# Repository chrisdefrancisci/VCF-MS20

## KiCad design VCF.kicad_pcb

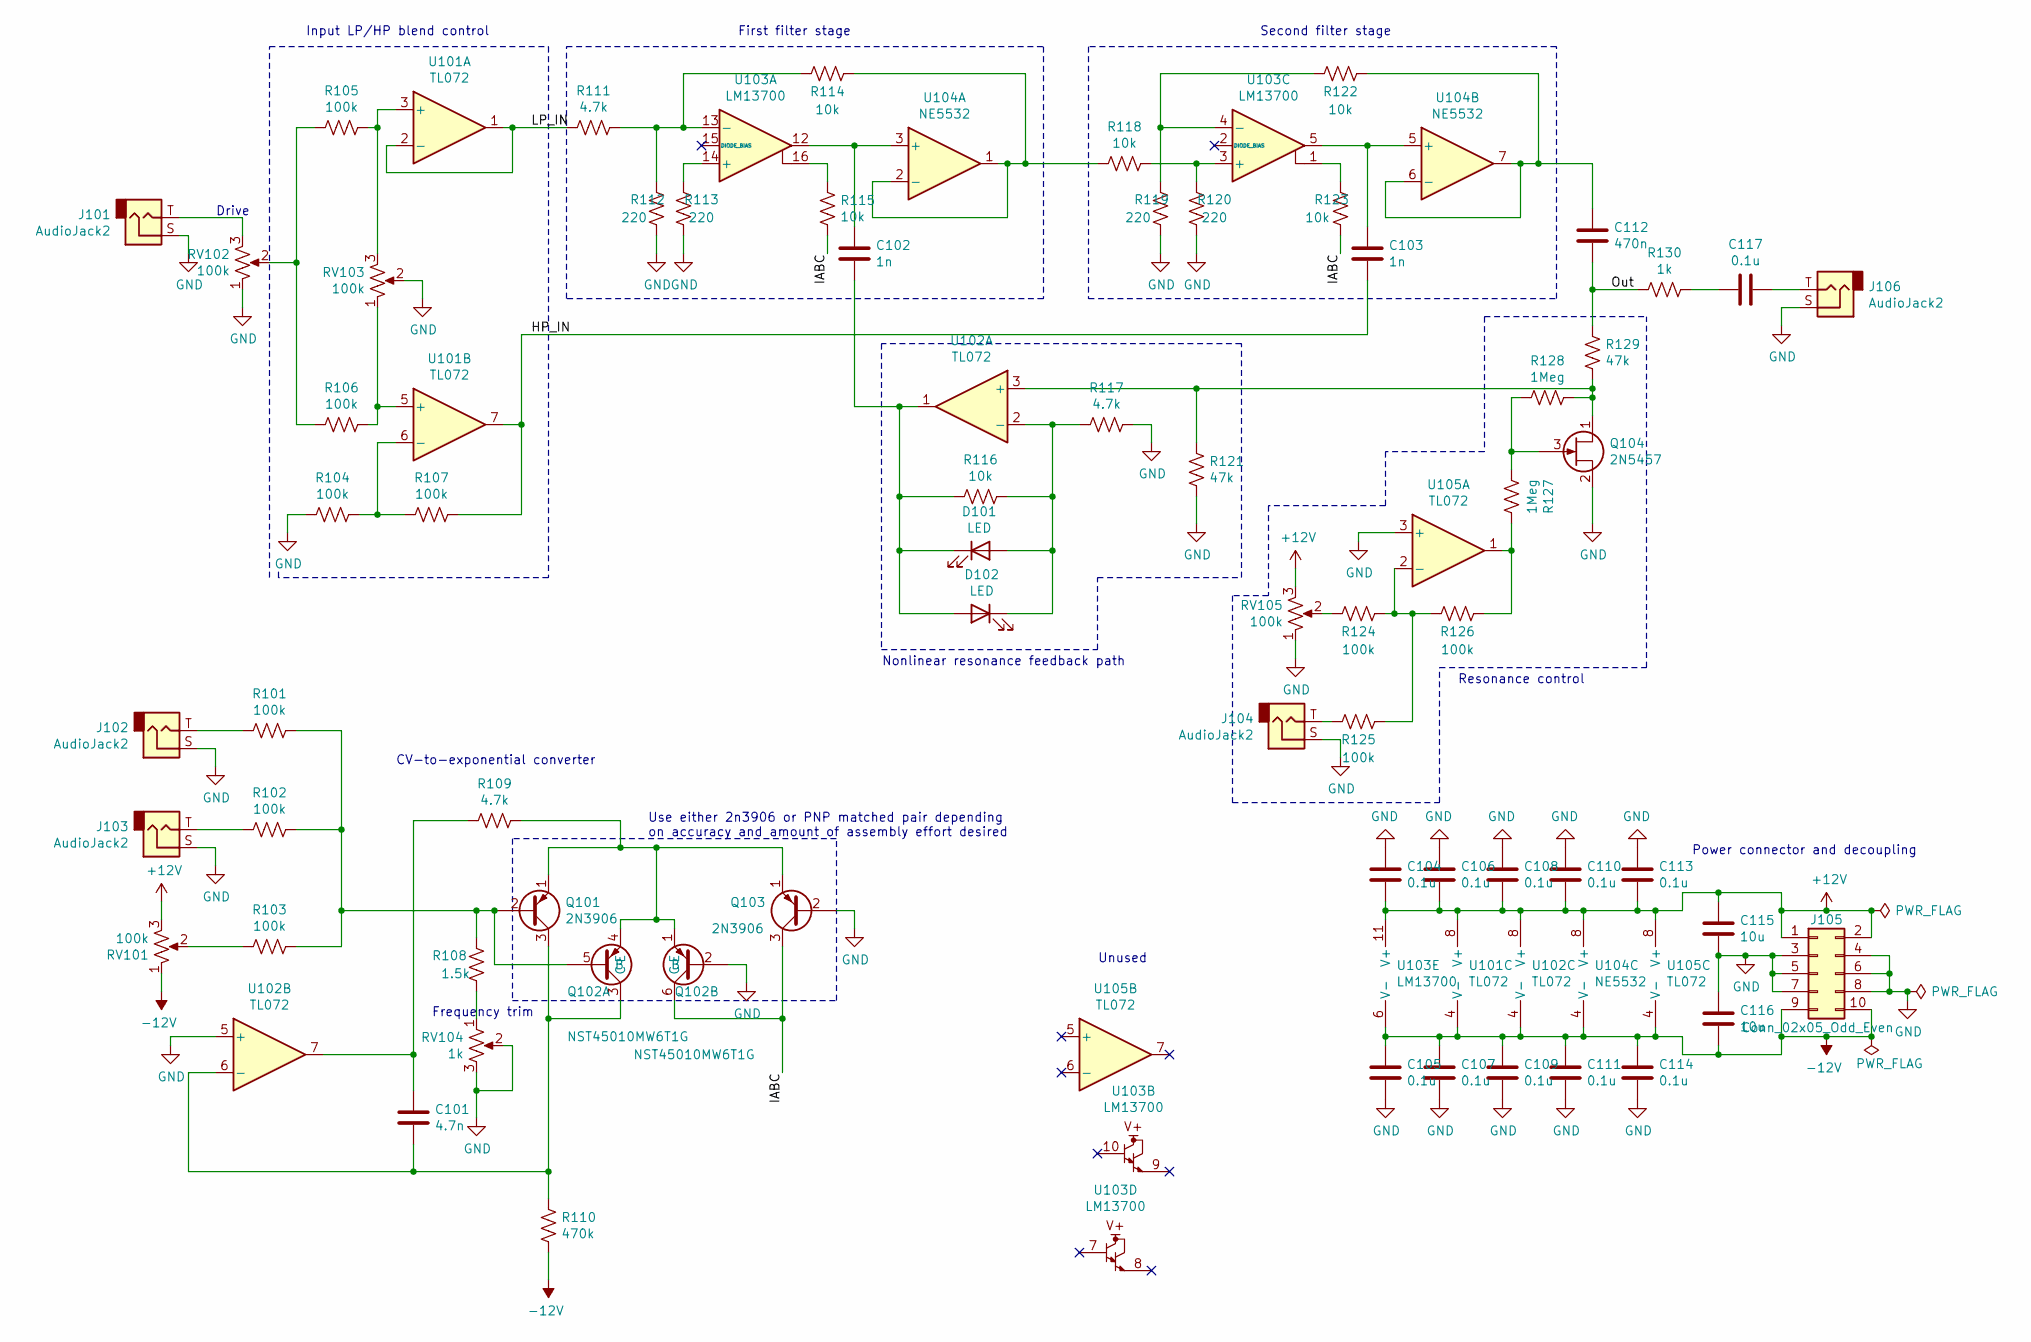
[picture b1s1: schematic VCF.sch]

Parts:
C101: 4.7n; C_0402_1005Metric; LCSC C1538
C102, C103: 1n; C_0402_1005Metric; LCSC C1523
C104, C105, C106, C107, C108, C109, C110, C111, C113, C114, C117: 0.1u; C_0402_1005Metric; LCSC C1525
C112: 470n; C_0402_1005Metric; LCSC C47339
C115, C116: 10u; C_0402_1005Metric; LCSC C15525
D101, D102: LED; LED_D5.0mm
J101, J102, J103, J104, J106: AudioJack2; A-2563
J105: Conn_02x05_Odd_Even; PinHeader_2x05_P2.54mm_Vertical
Q101, Q103: 2N3906; TO-92_Inline
Q102: NST45010MW6T1G; SOT-363_SC-70-6_Handsoldering
Q104: 2N5457; TO-92_Inline
R101, R102, R103, R104, R105, R106, R107, R124, R125, R126: 100k; R_0402_1005Metric; LCSC C25741
R108: 1.5k; R_0402_1005Metric; LCSC C25867
R109, R111, R117: 4.7k; R_0402_1005Metric; LCSC C25900
R110: 470k; R_0402_1005Metric; LCSC C25792
R112, R113, R119, R120: 220; R_0402_1005Metric; LCSC C25091
R114, R115, R116, R118, R122, R123: 10k; R_0402_1005Metric; LCSC C25744
R121, R129: 47k; R_0402_1005Metric; LCSC C25792
R127, R128: 1Meg; R_0402_1005Metric; LCSC C26083
R130: 1k; R_0402_1005Metric; LCSC C11702
RV101, RV102, RV103, RV105: 100k; A-5513
RV104: 1k; Potentiometer_Bourns_3296X_Horizontal
U101, U102, U105: TL072; SOIC-8_3.9x4.9mm_P1.27mm; LCSC C6961
U103: LM13700; DIP-16_W7.62mm
U104: NE5532; SOIC-8_3.9x4.9mm_P1.27mm; LCSC C7426

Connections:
+12V: C104.2, C106.2, C108.2, C110.2, C113.2, C115.1, J105.1, J105.2, RV101.3, RV105.3, U101.8 (V+), U102.8 (V+), U103.11 (V+), U104.8 (V+), U105.8 (V+)
-12V: C105.1, C107.1, C109.1, C111.1, C114.1, C116.2, J105.9, J105.10, R110.2, RV101.1, U101.4 (V-), U102.4 (V-), U103.6 (V-), U104.4 (V-), U105.4 (V-)
/HP_IN: C103.2, R107.1, U101.7
/IABC: Q102.6 (C), Q103.3 (C), R115.2, R123.2
/LP_IN: R111.2, U101.1, U101.2 (-)
/Out: C112.1, R129.2, R130.2
GND: C104.1, C105.2, C106.1, C107.2, C108.1, C109.2, C110.1, C111.2, C113.1, C114.2, C115.2, C116.1, J101.S, J102.S, J103.S, J104.S, J105.3, J105.4, J105.5, J105.6, J105.7, J105.8, J106.S, Q102.2 (B), Q103.2 (B), Q104.2 (S), R104.2, R112.2, R113.2, R117.2, R119.2, R120.2, R121.1, RV102.1, RV103.2, RV104.2, RV104.3, RV105.1, U102.5 (+), U105.3 (+)
unnamed: C101.1, R109.2, U102.7
unnamed: C101.2, Q101.3 (C), Q102.3 (C), R110.1, U102.6 (-)
unnamed: C102.1, U103.12, U104.3 (+)
unnamed: C102.2, D101.1 (K), D102.2 (A), R116.2, U102.1
unnamed: C103.1, U103.5, U104.5 (+)
unnamed: C112.2, R122.1, U104.6 (-), U104.7
unnamed: C117.1, J106.T
unnamed: C117.2, R130.1
unnamed: D101.2 (A), D102.1 (K), R116.1, R117.1, U102.2 (-)
unnamed: J101.T, RV102.3
unnamed: J102.T, R101.2
unnamed: J103.T, R102.2
unnamed: J104.T, R125.1
unnamed: Q101.1 (E), Q102.1 (E), Q102.4 (E), Q103.1 (E), R109.1
unnamed: Q101.2 (B), Q102.5 (B), R101.1, R102.1, R103.1, R108.1
unnamed: Q104.1 (D), R121.2, R128.1, R129.1, U102.3 (+)
unnamed: Q104.3 (G), R127.2, R128.2
unnamed: R103.2, RV101.2
unnamed: R104.1, R107.2, U101.6 (-)
unnamed: R105.1, RV103.3, U101.3 (+)
unnamed: R105.2, R106.2, RV102.2
unnamed: R106.1, RV103.1, U101.5 (+)
unnamed: R108.2, RV104.1
unnamed: R111.1, R112.1, R114.2, U103.13 (-)
unnamed: R113.1, U103.14 (+)
unnamed: R114.1, R118.2, U104.1, U104.2 (-)
unnamed: R115.1, U103.16
unnamed: R118.1, R120.1, U103.3 (+)
unnamed: R119.1, R122.2, U103.4 (-)
unnamed: R123.1, U103.1
unnamed: R124.1, RV105.2
unnamed: R124.2, R125.2, R126.1, U105.2 (-)
unnamed: R126.2, R127.1, U105.1

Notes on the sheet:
Input LP/HP blend control
Drive
First filter stage
Second filter stage
Resonance control
Nonlinear resonance feedback path
CV-to-exponential converter
Unused
Power connector and decoupling
Frequency trim
Use either 2n3906 or PNP matched pair depending on accuracy and amount of assembly effort desired

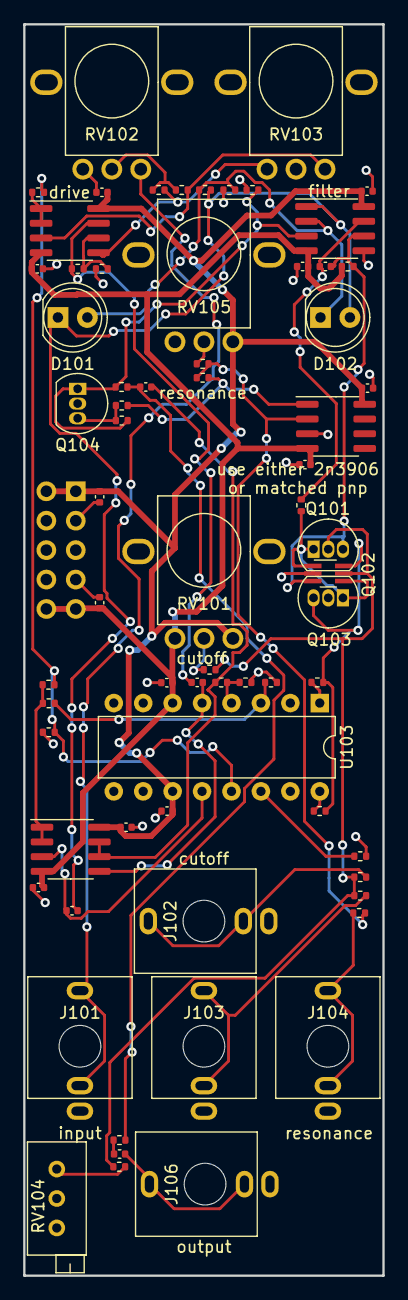
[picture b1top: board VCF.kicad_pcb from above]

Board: 2 copper layers, 31.0 x 108.0 mm, 69 parts (1 on the bottom side), 40 nets.

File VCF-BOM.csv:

Comment,Designator,Footprint,LCSC
"4.7n","C101","Capacitor_SMD:C_0402_1005Metric","C1538"
"1n","C102,C103","Capacitor_SMD:C_0402_1005Metric","C1523"
"470n","C112","Capacitor_SMD:C_0402_1005Metric","C47339"
"10u","C115,C116","Capacitor_SMD:C_0402_1005Metric","C15525"
"0.1u","C104,C105,C106,C107,C108,C109,C110,C111,C113,C114,C117","Capacitor_SMD:C_0402_1005Metric","C1525"
"LED","D101,D102","LED_THT:LED_D5.0mm",""
"AudioJack2","J101,J102,J103,J104,J106","A-2563:A-2563",""
"Conn_02x05_Odd_Even","J105","Connector_PinHeader_2.54mm:PinHeader_2x05_P2.54mm_Vertical",""
"NST45010MW6T1G","Q102","Package_TO_SOT_SMD:SOT-363_SC-70-6_Handsoldering",""
"2N3906","Q101,Q103","Package_TO_SOT_THT:TO-92_Inline",""
"2N5457","Q104","Package_TO_SOT_THT:TO-92_Inline",""
"100k","R101,R102,R103,R104,R105,R106,R107,R124,R125,R126","Resistor_SMD:R_0402_1005Metric","C25741"
"1.5k","R108","Resistor_SMD:R_0402_1005Metric","C25867"
"470k","R110","Resistor_SMD:R_0402_1005Metric","C25792"
"4.7k","R109,R111,R117","Resistor_SMD:R_0402_1005Metric","C25900"
"220","R112,R113,R119,R120","Resistor_SMD:R_0402_1005Metric","C25091"
"10k","R114,R115,R116,R118,R122,R123","Resistor_SMD:R_0402_1005Metric","C25744"
"47k","R121,R129","Resistor_SMD:R_0402_1005Metric","C25792"
"1Meg","R127,R128","Resistor_SMD:R_0402_1005Metric","C26083"
"1k","R130","Resistor_SMD:R_0402_1005Metric","C11702"
"100k","RV101,RV102,RV103,RV105","A-5513:A-5513",""
"1k","RV104","Potentiometer_THT:Potentiometer_Bourns_3296X_Horizontal",""
"TL072","U101,U102,U105","Package_SO:SOIC-8_3.9x4.9mm_P1.27mm","C6961"
"LM13700","U103","Package_DIP:DIP-16_W7.62mm",""
"NE5532","U104","Package_SO:SOIC-8_3.9x4.9mm_P1.27mm","C7426"

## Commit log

2021-05-18 Finished schematic including CV resonance
2021-05-18 Added SMT option for PNP current mirror
2021-05-18 Assigned footprints to all components
2021-05-19 Finished pcb design
2021-05-19 Generated gerbers and manufacturing files
2021-06-01 fixed backwards cutoff frequency potentiometer
